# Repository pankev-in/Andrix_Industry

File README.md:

# Andrix_Industry
AndriX in Industry Use - Practical Robotics Institute Austria (PRIA)

# About this Repository
Here you can find all files, Software and complete documentations used in this Project. Here is a link to a Youtube 
Video, where you can see it in action:
<a href="https://www.youtube.com/watch?v=nksSCDoHSoU">Hedgehog controller drives industrial motor (SCORE! project)</a>

# Who is PRIA?
The Practical Robotics Institute Austria (PRIA) is a non-profit organisation with the aim to promote scien-
tific and technical excellence in schools using robotics as well as the participation and operation of exemplary
research projects in fields related to robotics and automation and teaching methods by means of robotics.
The Practical Robotics Institute Austria is constituted as an independent non-profit organisation with a
scientific advisory board.

# Concept of this Project
Nowadays computers with ARM architecture are becomming more common. Various smartphones, as well
as sigle-board computers like Raspberry Pi are becomming cheaper and much more affordable. To be able
to use ARM Devices as robot controllers, some additional hardware that enables connecting and controlling
robot components such as sensors, motors and servos are required. The hardware (aka. Low-Level Control,
LLC) and the ARM devices(aka. High-Level Control, HLC) should be able to be connected together using
both wired and wireless communications.

Andrix Industry is the concept of implementing this kind of structure in an industrial environment and
its controller has to be relatively low-cost, stable and expandable for different uses.
In this project, we use a standard industrial conveyor belt to test our idea. We will connect our Andrix
controller (including an Raspberry Pi as the High level control) to an external Motor Controller (aka. Ex-
ternal Hardware Controller level) to be able to drive the conveyor belt using a Stepper Motor.

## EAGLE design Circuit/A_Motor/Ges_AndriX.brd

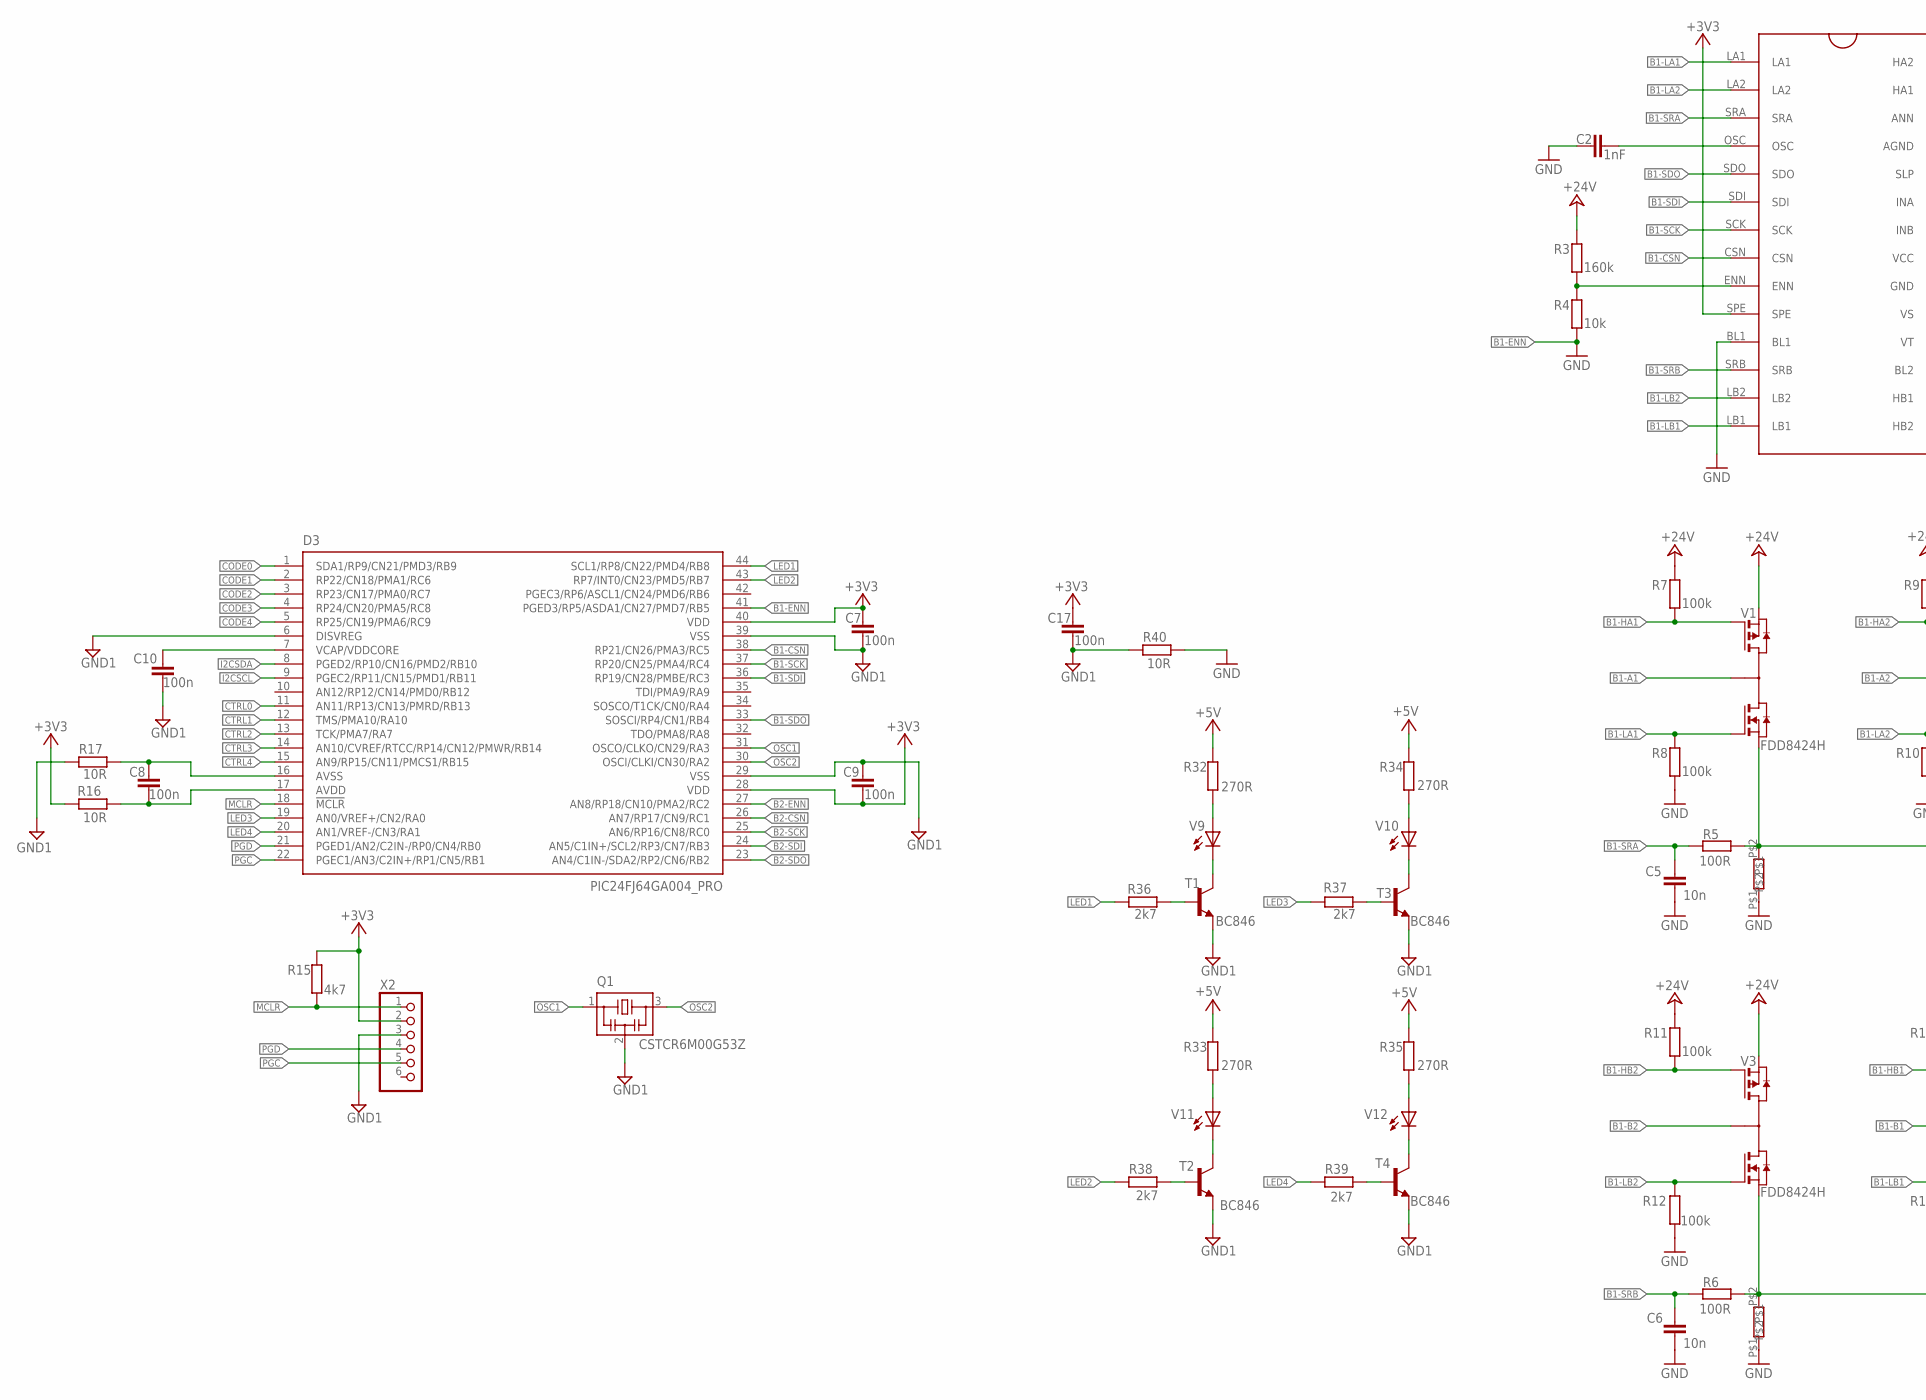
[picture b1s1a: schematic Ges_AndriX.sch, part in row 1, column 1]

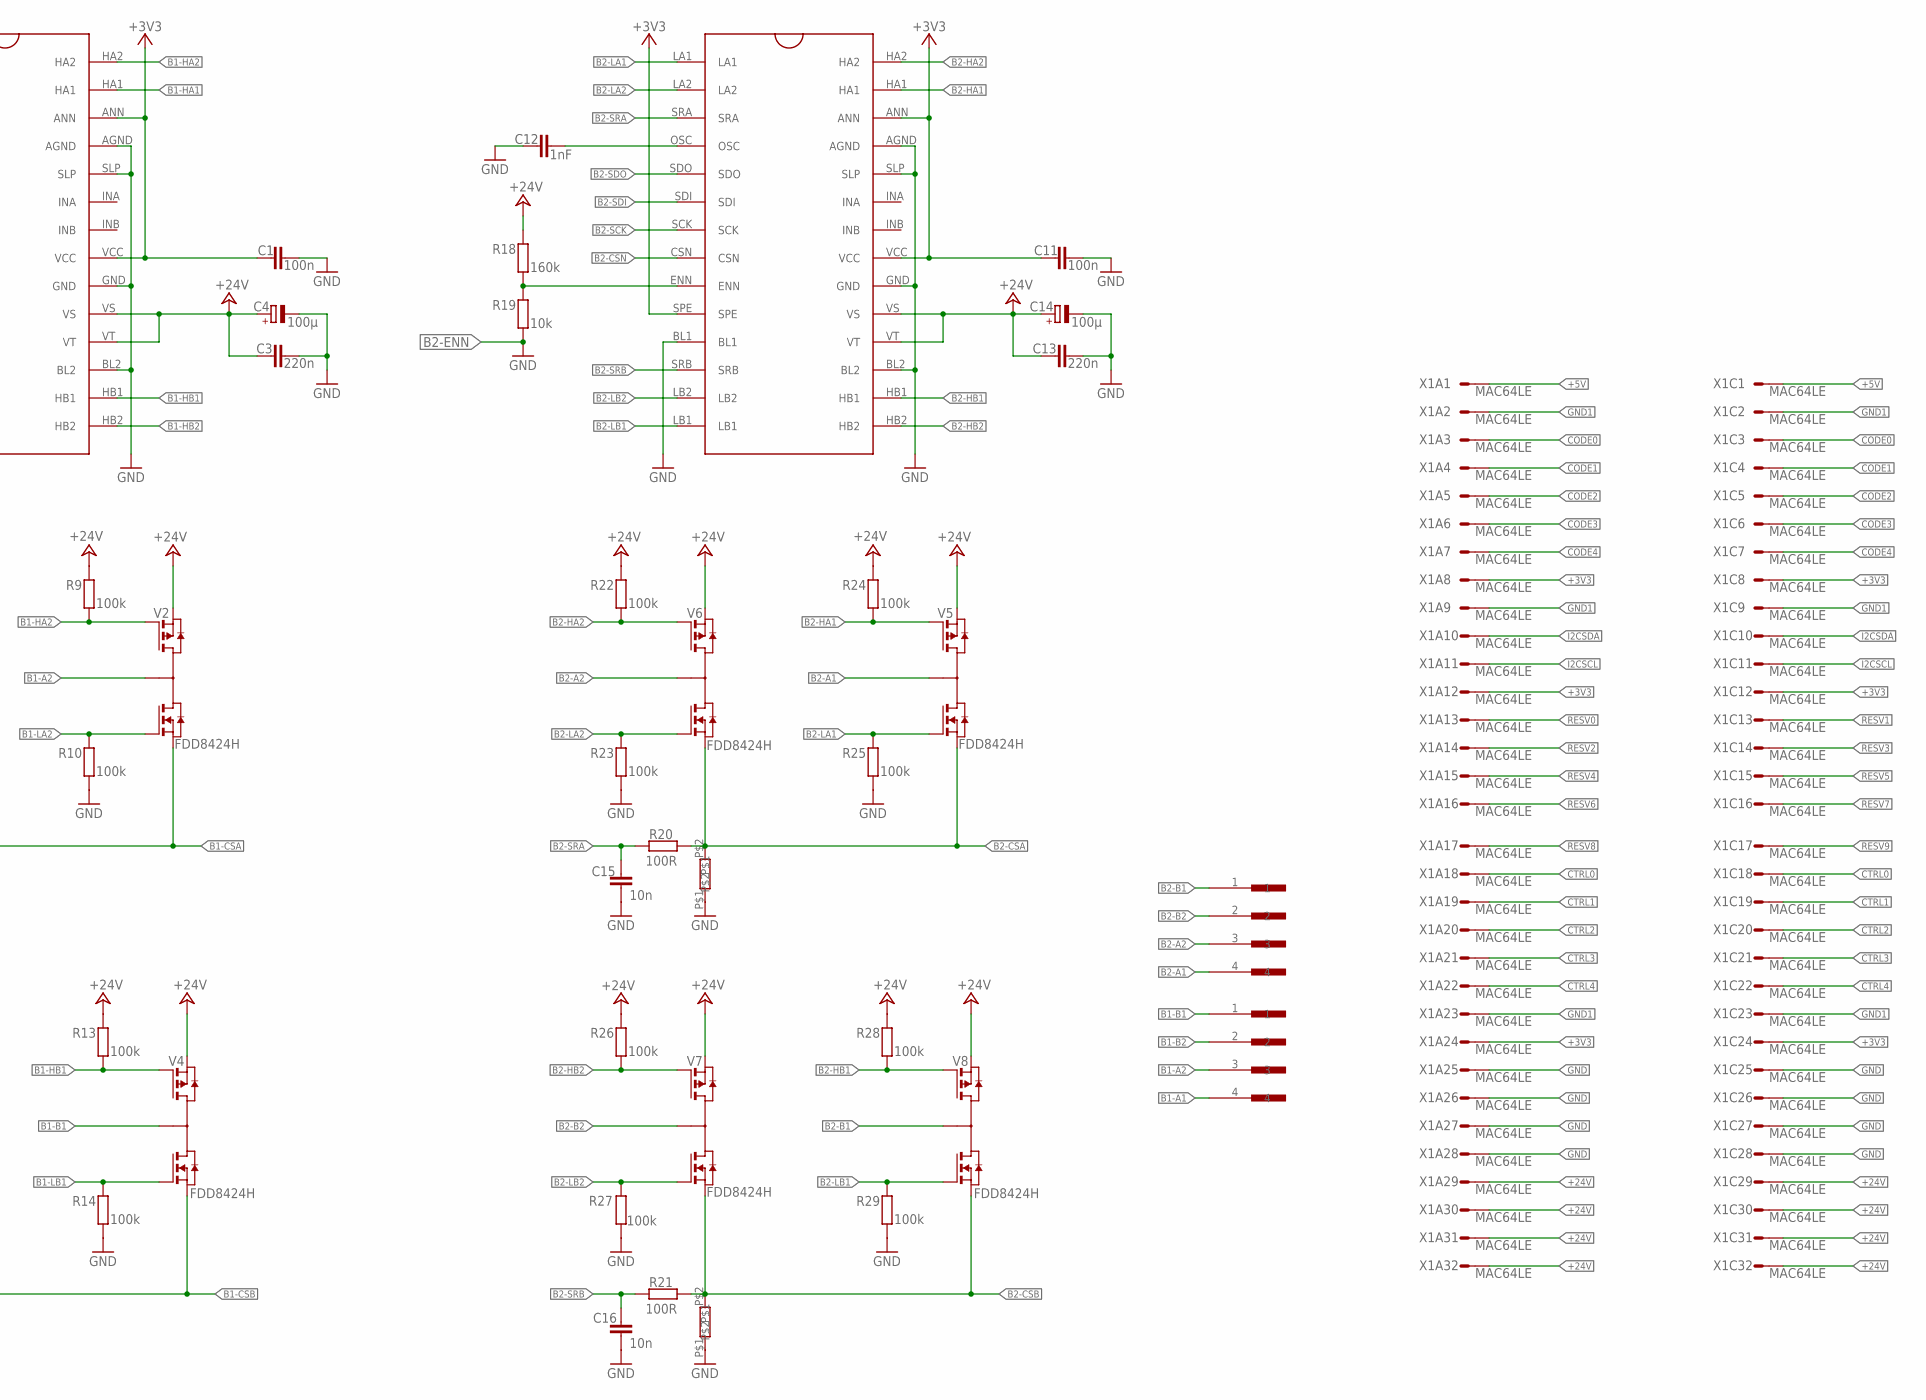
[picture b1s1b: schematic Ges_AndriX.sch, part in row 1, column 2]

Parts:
C1, C11: 100n; C1206
C2, C12: 1nF; C1206
C3, C13: 220n; C1206
C4, C14: 100µ; 140CLH-1010
C5, C6, C15, C16: 10n; C1206
C7, C8, C9, C10, C17: 100n; C1206K
D1, D2: TMC249; SO28
D3: PIC24FJ64GA004_PRO; TQFP44
Q1: CSTCR6M00G53Z; CSTER12M
R1, R2, R30, R31: 30m; RS
R3, R18: 160k; M1206
R4, R19: 10k; M1206
R5, R6, R20, R21: 100R; M1206
R7, R8, R9, R10, R11, R12, R13, R14, R22, R23, R24, R25, R26, R27, R28, R29: 100k; R1206
R15: 4k7; M1206
R16, R17, R40: 10R; M1206
R32, R33, R34, R35: 270R; M1206
R36, R37, R38, R39: 2k7; M1206
T1, T2, T3, T4: BC846; SOT23
V1, V2, V3, V4, V5, V6, V7, V8: FDD8424H; TO-252-4L
V9, V10, V11, V12: LEDCHIPLED_1206; CHIPLED_1206
X1: MAC64LE; MAC64L
X2: PINHD-1X6; 1X06
X3, X4: X_4POL

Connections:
+3V3: C1.1, C7.2, C9.2, C11.1, C17.2, D1.ANN, D1.SPE, D1.VCC, D2.ANN, D2.SPE, D2.VCC, D3.28 (VDD), D3.40 (VDD), R15.2, R16.2, X1.A8, X1.A12, X1.A24, X1.C8, X1.C12, X1.C24, X2.2
+5V: R32.2, R33.2, R34.2, R35.2, X1.A1, X1.C1
+24V: C3.1, C4.+, C13.1, C14.+, D1.VS, D1.VT, D2.VS, D2.VT, R3.2, R7.2, R9.2, R11.2, R13.2, R18.2, R22.2, R24.2, R26.2, R28.2, V1.S2, V2.S2, V3.S2, V4.S2, V5.S2, V6.S2, V7.S2, V8.S2, X1.A29, X1.A30, X1.A31, X1.A32, X1.C29, X1.C30, X1.C31, X1.C32
B1-A1: V1.D1D2, X4.4
B1-A2: V2.D1D2, X4.3
B1-B1: V4.D1D2, X4.1
B1-B2: V3.D1D2, X4.2
B1-CSA: R2.P$2, R5.2, V1.S1, V2.S1
B1-CSB: R1.P$2, R6.2, V3.S1, V4.S1
B1-CSN: D2.CSN, D3.38 (RP21/CN26/PMA3/RC5)
B1-ENN: D3.41 (PGED3/RP5/ASDA1/CN27/PMD7/RB5), R4.1
B1-HA1: D2.HA1, R7.1, V1.G2
B1-HA2: D2.HA2, R9.1, V2.G2
B1-HB1: D2.HB1, R13.1, V4.G2
B1-HB2: D2.HB2, R11.1, V3.G2
B1-LA1: D2.LA1, R8.2, V1.G1
B1-LA2: D2.LA2, R10.2, V2.G1
B1-LB1: D2.LB1, R14.2, V4.G1
B1-LB2: D2.LB2, R12.2, V3.G1
B1-SCK: D2.SCK, D3.37 (RP20/CN25/PMA4/RC4)
B1-SDI: D2.SDI, D3.36 (RP19/CN28/PMBE/RC3)
B1-SDO: D2.SDO, D3.33 (SOSCI/RP4/CN1/RB4)
B1-SRA: C5.1, D2.SRA, R5.1
B1-SRB: C6.1, D2.SRB, R6.1
B2-A1: V5.D1D2, X3.4
B2-A2: V6.D1D2, X3.3
B2-B1: V8.D1D2, X3.1
B2-B2: V7.D1D2, X3.2
B2-CSA: R20.2, R30.P$2, V5.S1, V6.S1
B2-CSB: R21.2, R31.P$2, V7.S1, V8.S1
B2-CSN: D1.CSN, D3.26 (AN7/RP17/CN9/RC1)
B2-ENN: D3.27 (AN8/RP18/CN10/PMA2/RC2), R19.1
B2-HA1: D1.HA1, R24.1, V5.G2
B2-HA2: D1.HA2, R22.1, V6.G2
B2-HB1: D1.HB1, R28.1, V8.G2
B2-HB2: D1.HB2, R26.1, V7.G2
B2-LA1: D1.LA1, R25.2, V5.G1
B2-LA2: D1.LA2, R23.2, V6.G1
B2-LB1: D1.LB1, R29.2, V8.G1
B2-LB2: D1.LB2, R27.2, V7.G1
B2-SCK: D1.SCK, D3.25 (AN6/RP16/CN8/RC0)
B2-SDI: D1.SDI, D3.24 (AN5/C1IN+/SCL2/RP3/CN7/RB3)
B2-SDO: D1.SDO, D3.23 (AN4/C1IN-/SDA2/RP2/CN6/RB2)
B2-SRA: C15.1, D1.SRA, R20.1
B2-SRB: C16.1, D1.SRB, R21.1
CODE0: D3.1 (SDA1/RP9/CN21/PMD3/RB9), X1.A3, X1.C3
CODE1: D3.2 (RP22/CN18/PMA1/RC6), X1.A4, X1.C4
CODE2: D3.3 (RP23/CN17/PMA0/RC7), X1.A5, X1.C5
CODE3: D3.4 (RP24/CN20/PMA5/RC8), X1.A6, X1.C6
CODE4: D3.5 (RP25/CN19/PMA6/RC9), X1.A7, X1.C7
CTRL0: D3.11 (AN11/RP13/CN13/PMRD/RB13), X1.A18, X1.C18
CTRL1: D3.12 (TMS/PMA10/RA10), X1.A19, X1.C19
CTRL2: D3.13 (TCK/PMA7/RA7), X1.A20, X1.C20
CTRL3: D3.14 (AN10/CVREF/RTCC/RP14/CN12/PMWR/RB14), X1.A21, X1.C21
CTRL4: D3.15 (AN9/RP15/CN11/PMCS1/RB15), X1.A22, X1.C22
GND: C1.2, C2.2, C3.2, C4.-, C5.2, C6.2, C11.2, C12.2, C13.2, C14.-, C15.2, C16.2, D1.AGND, D1.BL1, D1.BL2, D1.GND, D1.SLP, D2.AGND, D2.BL1, D2.BL2, D2.GND, D2.SLP, R1.P$1, R2.P$1, R8.1, R10.1, R12.1, R14.1, R23.1, R25.1, R27.1, R29.1, R30.P$1, R31.P$1, R40.1, X1.A25, X1.A26, X1.A27, X1.A28, X1.C25, X1.C26, X1.C27, X1.C28
GND1: C7.1, C9.1, C10.2, C17.1, D3.6 (DISVREG), D3.29 (VSS), D3.39 (VSS), Q1.2, R17.2, R40.2, T1.2 (E), T2.2 (E), T3.2 (E), T4.2 (E), X1.A2, X1.A9, X1.A23, X1.C2, X1.C9, X1.C23, X2.3
I2CSCL: D3.9 (PGEC2/RP11/CN15/PMD1/RB11), X1.A11, X1.C11
I2CSDA: D3.8 (PGED2/RP10/CN16/PMD2/RB10), X1.A10, X1.C10
LED1: D3.44 (SCL1/RP8/CN22/PMD4/RB8), R36.2
LED2: D3.43 (RP7/INT0/CN23/PMD5/RB7), R38.1
LED3: D3.19 (AN0/VREF+/CN2/RA0), R37.2
LED4: D3.20 (AN1/VREF-/CN3/RA1), R39.2
MCLR: D3.18 (!MCLR), R15.1, X2.1
unnamed: C2.1, D2.OSC
unnamed: C8.2, D3.17 (AVDD), R16.1
unnamed: C8.1, D3.16 (AVSS), R17.1
unnamed: C10.1, D3.7 (VCAP/VDDCORE)
unnamed: T1.3 (C), V9.C
unnamed: C12.1, D1.OSC
unnamed: T2.3 (C), V11.C
unnamed: T3.3 (C), V10.C
unnamed: D1.ENN, R18.1, R19.2
unnamed: T4.3 (C), V12.C
unnamed: R32.1, V9.A
unnamed: R33.1, V11.A
unnamed: R34.1, V10.A
unnamed: R35.1, V12.A
unnamed: R36.1, T1.1 (B)
unnamed: D2.ENN, R3.1, R4.2
unnamed: R37.1, T3.1 (B)
unnamed: R38.2, T2.1 (B)
unnamed: R39.1, T4.1 (B)
OSC1: D3.31 (OSCO/CLKO/CN29/RA3), Q1.1
OSC2: D3.30 (OSCI/CLKI/CN30/RA2), Q1.3
PGC: D3.22 (PGEC1/AN3/C2IN+/RP1/CN5/RB1), X2.5
PGD: D3.21 (PGED1/AN2/C2IN-/RP0/CN4/RB0), X2.4
RESV0: X1.A13
RESV1: X1.C13
RESV2: X1.A14
RESV3: X1.C14
RESV4: X1.A15
RESV5: X1.C15
RESV6: X1.A16
RESV7: X1.C16
RESV8: X1.A17
RESV9: X1.C17

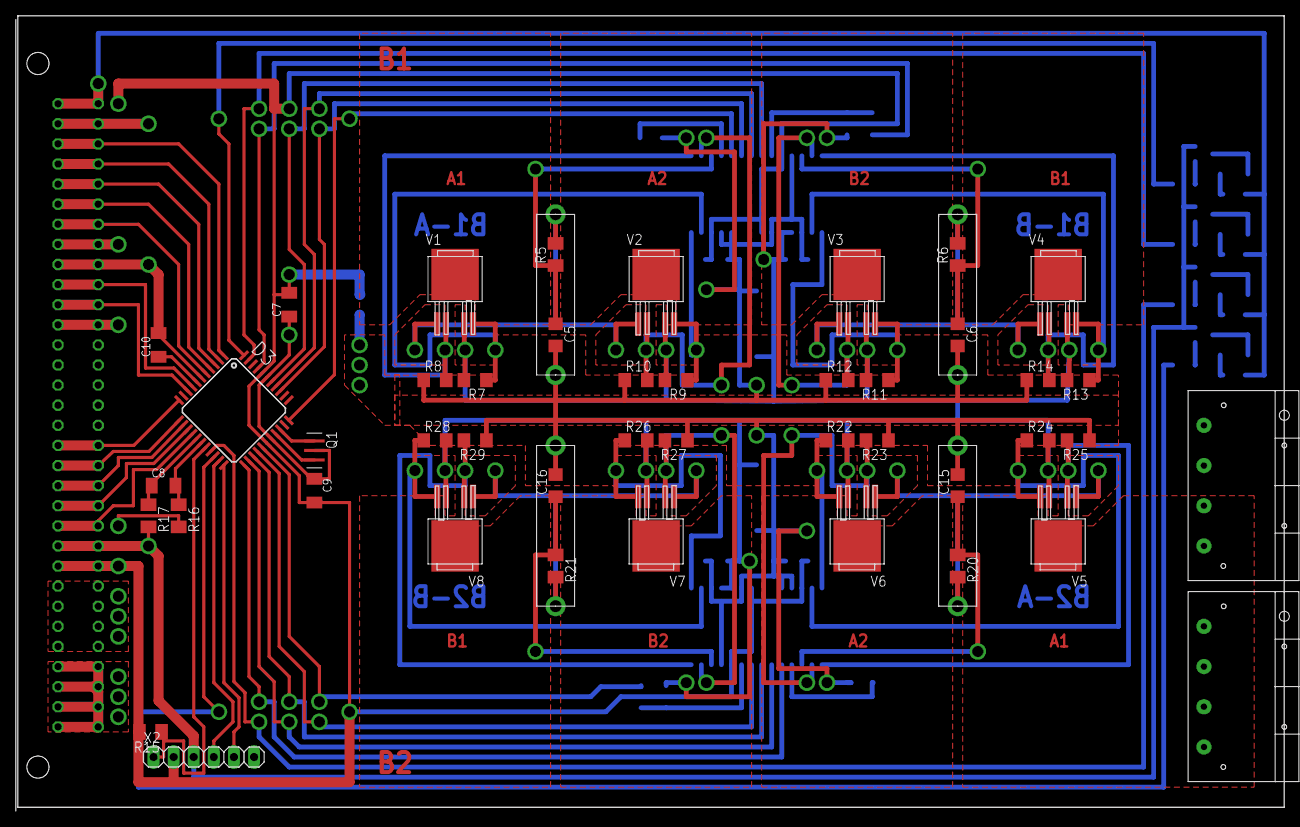
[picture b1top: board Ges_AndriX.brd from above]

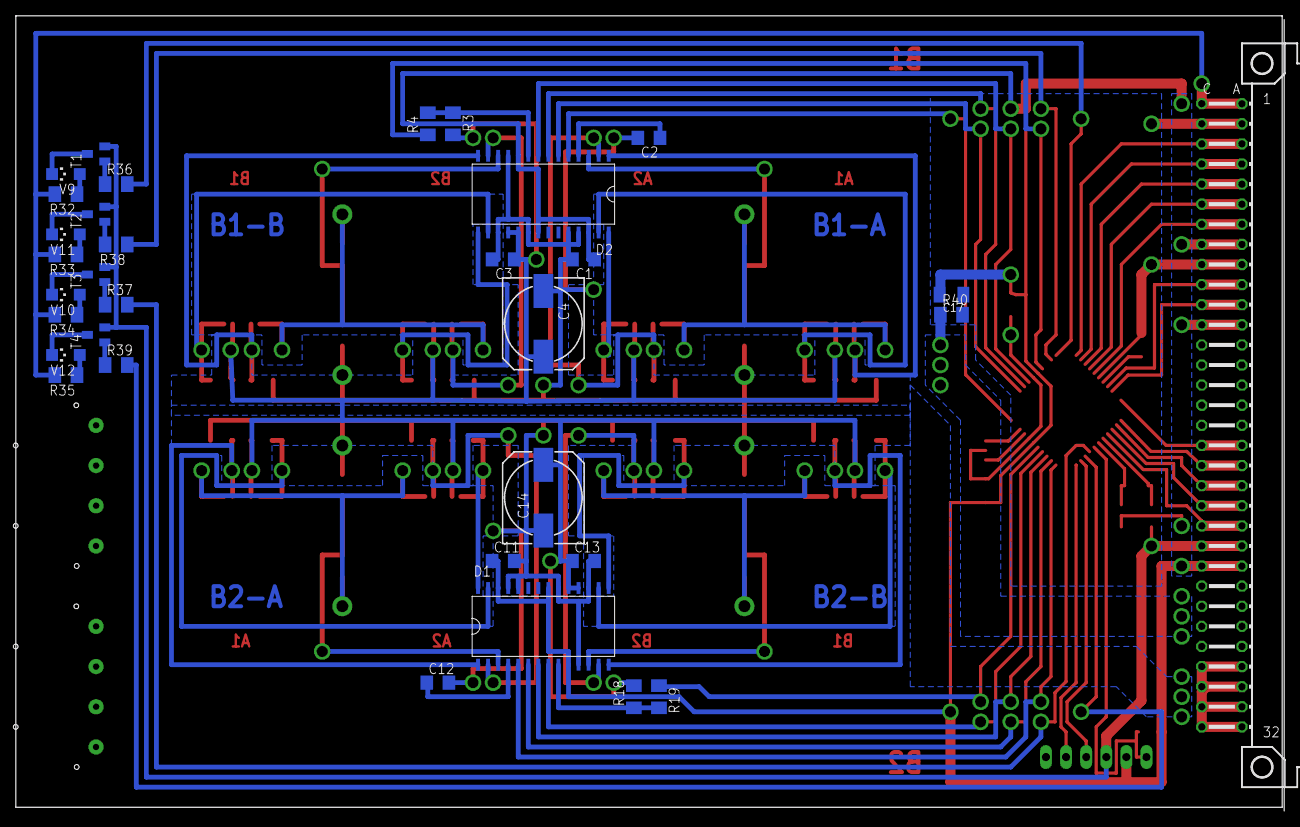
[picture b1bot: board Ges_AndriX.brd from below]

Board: 2 copper layers, 160.0 x 100.0 mm, 81 parts (33 on the bottom side), 87 nets.

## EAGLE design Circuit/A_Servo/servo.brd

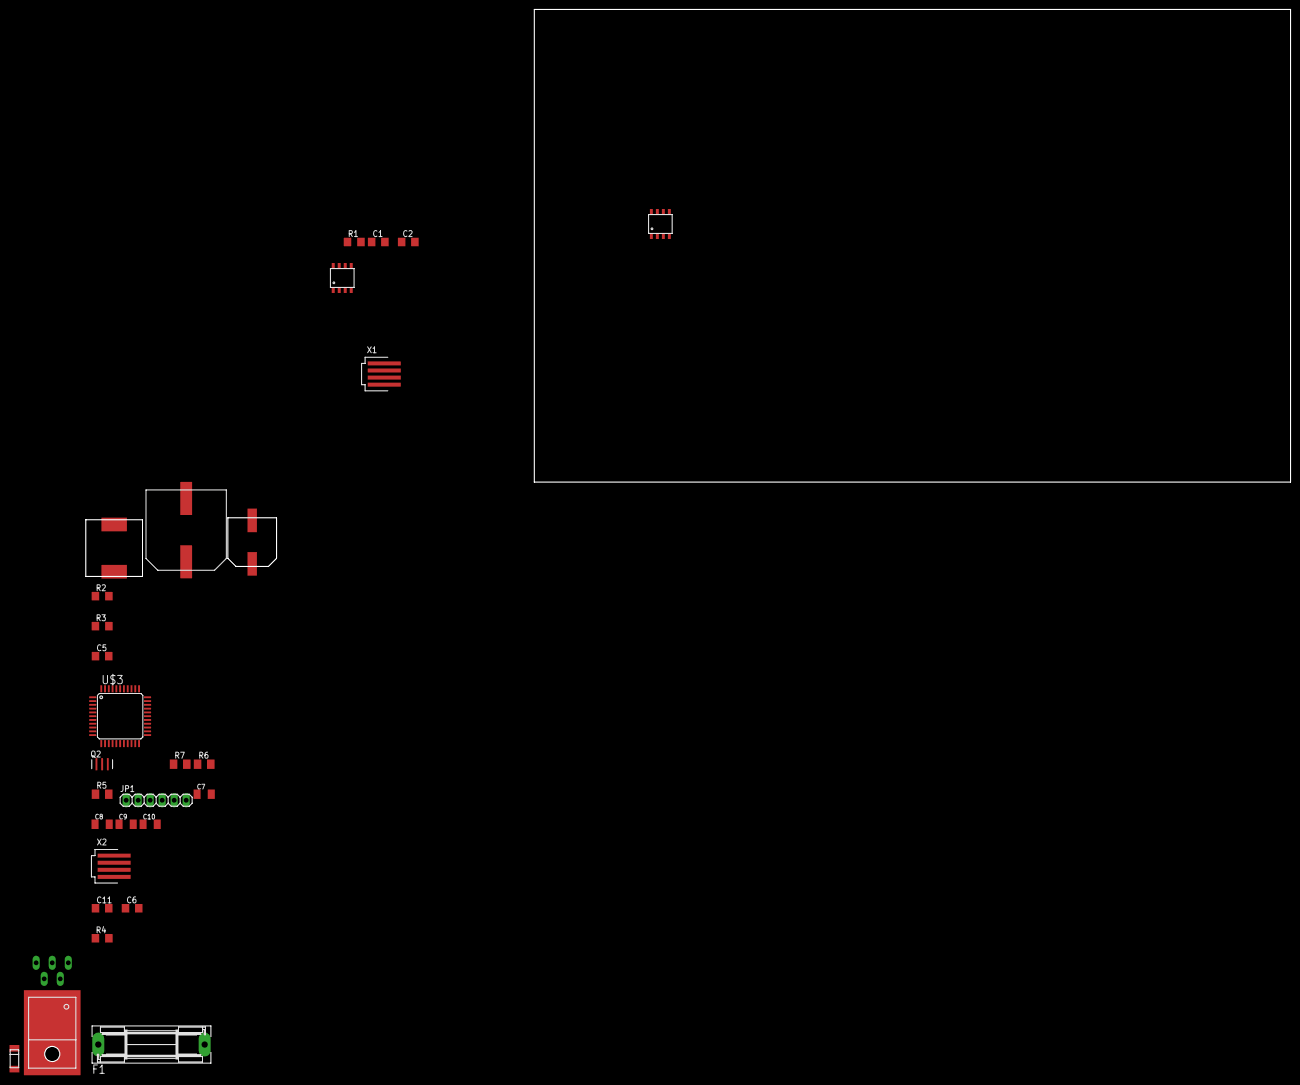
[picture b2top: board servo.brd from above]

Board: 2 copper layers, 29 parts (0 on the bottom side), 23 nets, no tracks yet.

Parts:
C1, C6: 2m2; C1206
C2, C5, C11: 100n; C1206
C3: 220uF; C220
C4: 680uF; C680
C7, C8, C9, C10: 100n; C1206K
F1: SH22,5
JP1: 1X06
L1: WE-PD
N2, N3: MAX485; SO08
Q2: CSTCR6M00G53Z; CSTER12M
R1, R4: 10k; R1206
R2: 1k; R1206
R3: 13.7k; R1206
R5, R6: 10R; M1206
R7: 4k7; M1206
U$1: LM2596; TO220
U$2: SCHOTTKY
U$3: PIC24FJ64GA004_PRO; TQFP44
X1, X2: 87438-04

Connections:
+3V3: C7.2, C9.2, JP1.2, R6.2, R7.2, U$3.28, U$3.40
+5V: C2.1, C11.1, N2.VCC, N3.VCC, R1.2, R4.2
GND: C1.2, C2.2, C3.-, C4.-, C6.2, C7.1, C9.1, C10.2, C11.2, JP1.3, N2.GND, N3.GND, Q2.2, R2.2, R5.2, U$1.GND, U$1.GNDB, U$1.ON/OFF, U$2.-, U$3.6, U$3.29, U$3.39, X1.1, X2.1
MCLR: JP1.1, R7.1, U$3.18
unnamed: N2.DE, N2.RE/
unnamed: N2.RO, R1.1
unnamed: N2.A, X1.3
unnamed: C8.2, R6.1, U$3.17
unnamed: N2.B, X1.4
unnamed: C8.1, R5.1, U$3.16
unnamed: C4.+, F1.2, U$1.VIN
unnamed: C10.1, U$3.7
unnamed: C5.1, R2.1, R3.2, U$1.FB
unnamed: C5.2, L1.+, R3.1, U$1.VOUT, U$2.+
unnamed: N3.DE, N3.RE/
unnamed: N3.RO, R4.1
unnamed: N3.B, X2.4
unnamed: N3.A, X2.3
OSC1: Q2.1, U$3.30
OSC2: Q2.3, U$3.31
PGC: JP1.5, U$3.22
PGD: JP1.4, U$3.21
VM: C1.1, C3.+, C6.1, L1.-, X1.2, X2.2

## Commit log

2014-11-05 V1: Everything works with Arduino!!!
    Version 1: Prototype version
2014-11-05 V1.1 Working
2015-02-26 Clean up
2015-05-07 Final
2015-05-26 Finial Cleanup, Officially handed over to PRIA
